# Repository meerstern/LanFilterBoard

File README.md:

# LANフィルタ基板
LAN Filter Board

## 概要
 * 本基板はLANノイズフィルタの評価基板です  
 * LAN機器やケーブルから放射、伝搬されるノイズ、エミッションを低減させます
 * EMC試験やエミッション、伝導妨害試験等の対策検討に便利です  
 * Ethernet 100/1000BASE-Tに対応した360Ω@100MHzのコモンモードフィルタを実装しています  
 * 4ペアのコモンモードフィルタを実装しています  

## 使用方法
 * LAN機器のLANケーブル間に本フィルタを挿入して使用します   
 * 本フィルタはストレート結線です
 * ストレート結線のLANケーブルを使用してください
 * 4つのフィルタは基板に実装されているため、ハンダ付け不要です  
 
## 使用時の注意点
 * 本基板はフィルタの評価目的です  
 * 本基板を最終的な機器に組み込むことは想定していません  
 * 本基板はノイズ源に近い箇所に接続してください  
 * PoE環境での仕様は想定していません  
 * 使用方法によっては意図せず通信品質低下やエミッションが増加する場合があります  
 * 評価の際は本基板のエミッションを考慮した上で十分にシールドした状態で確認してください  
 * フィルタを含む表面実装部品に大きな力や衝撃を与えないように注意してください
 * 大きな力や衝撃によってフィルタが破損する場合があります  

## 詳細
 * 使用部品は下記です  
 * 告知なしに実装部品を後継品もしくは同等品に変更する場合があります  

| 部品 | 型式 | 仕様 | 
|:-----------|:------------|:------------|
| Port | [1149868][1] | Max 10 GBit/s |
| Filter | [ALC2012-361-2P-T00][2] | 360Ω@100MHz,DC 0.5Ω, Typ.220mA, [Link][3] |

## 外観
  * サイズ 約51mm x約30mm x約22mm(コネクタ含む) 

[1]: https://www.phoenixcontact.com/ja-jp/products/cuc-sp-j1st-a-r4lb-1149868
[2]: https://product.tdk.com/ja/search/emc/emc/cmf_cmc/info?part_no=ALC2012-361-2P-T00
[3]: https://product.tdk.com/ja/techlibrary/applicationnote/recommend_lan_cmf_cmc.html

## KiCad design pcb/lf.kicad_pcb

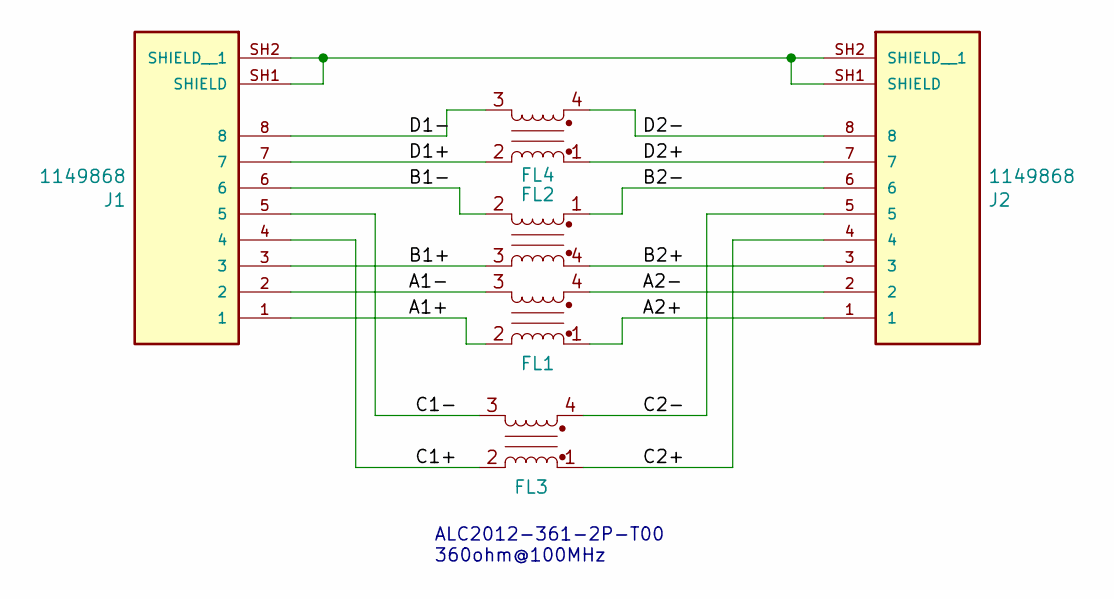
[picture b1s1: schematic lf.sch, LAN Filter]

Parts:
FL1, FL2, FL3, FL4: EMI_Filter_CommonMode; L_CommonModeChoke_Coilcraft_0805USB
J1, J2: 1149868; PARTREV 11.04.2022

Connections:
/A1+: FL1.2, J1.1
/A1-: FL1.3, J1.2
/A2+: FL1.1, J2.1
/A2-: FL1.4, J2.2
/B1+: FL2.3, J1.3
/B1-: FL2.2, J1.6
/B2+: FL2.4, J2.3
/B2-: FL2.1, J2.6
/C1+: FL3.2, J1.4
/C1-: FL3.3, J1.5
/C2+: FL3.1, J2.4
/C2-: FL3.4, J2.5
/D1+: FL4.2, J1.7
/D1-: FL4.3, J1.8
/D2+: FL4.1, J2.7
/D2-: FL4.4, J2.8
unnamed: J1.SH1 (SHIELD), J1.SH2 (SHIELD__1), J2.SH1 (SHIELD), J2.SH2 (SHIELD__1)

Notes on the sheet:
ALC2012-361-2P-T00 360ohm@100MHz

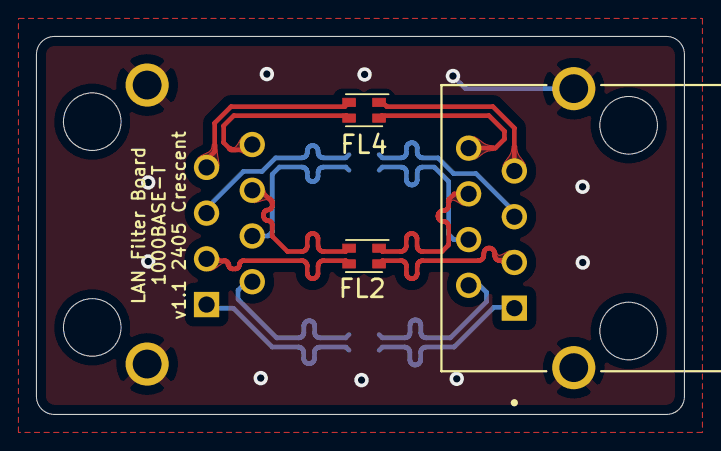
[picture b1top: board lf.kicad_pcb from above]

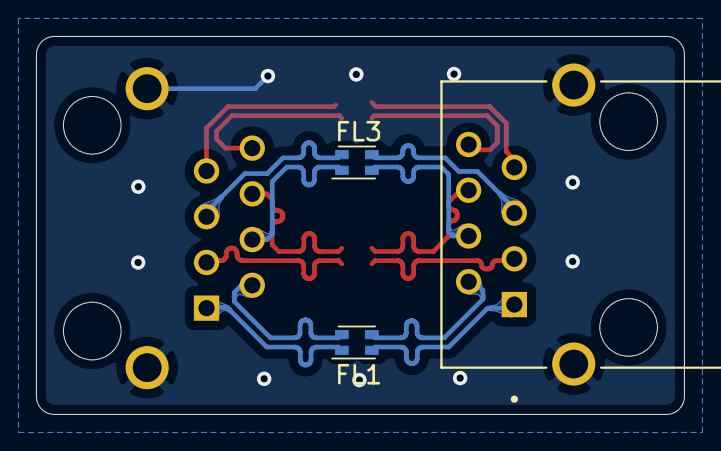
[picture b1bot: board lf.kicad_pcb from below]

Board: 2 copper layers, 36.0 x 21.0 mm, 6 parts (3 on the bottom side), 17 nets.

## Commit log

2024-06-04 Add Files
